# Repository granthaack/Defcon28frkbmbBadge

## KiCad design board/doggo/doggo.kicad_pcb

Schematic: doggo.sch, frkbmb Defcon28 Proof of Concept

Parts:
BT1: Battery_Cell
C1, C3, C4, C6: 100nF; C_0603_1608Metric
C2: 1uF; C_0805_2012Metric
C5: 220nF; C_0603_1608Metric
C7: 10uF
C8: 4.7uF
D1, D2, D3, D4, D5, D6, D7, D8, D9, D10, D11, D12, D13, D14, D15, D16, D17, D18, D19, D20, D21, D22, D23, D24, D25, D26, D27, D28, D29, D30, D31, D32, D33, D34, D35, D36, D37, D38, D39, D40, D41, D42, D43, D44, D45, D46, D47, D48, D49, D50, D51, D52, D53, D54, D55, D56, D57, D58, D59, D60, D61, D62, D63, D64, D65, D66, D67, D68, D69, D70, D71, D72, D73, D74, D75, D76, D77, D78, D79, D80, D81, D82, D83, D84, D85, D86, D87, D88, D89, D90, D91, D92, D93, D94, D95, D96, D97, D98, D99, D100, D101, D102, D103, D104, D105, D106, D107, D108, D109, D110, D111, D112, D113, D114, D115, D116, D117, D118, D119, D120, D121, D122, D123, D124, D125, D126, D127, D128, D129, D130, D131, D132, D133, D134, D135, D136, D137, D138, D139, D140, D141, D142, D143, D144: LED; D_0402_1005Metric
F1: Polyfuse
JP1: Jumper_2_Open
L1: 4.7uH
R1, R2, R3: 4.7k; R_0603_1608Metric
R4, R5: 100k; R_0603_1608Metric
R6, R32, R33: 1k; R_0603_1608Metric
R7: 536K; R_0603_1608Metric
R8: 309K; R_0603_1608Metric
SW1: SW_SPST
U1: IS31FL3731
U2: LIS2HH12
U3: STM32F042K6; LQFP-32_7x7mm_P0.8mm
U4: MCP1640; SOT-23-6

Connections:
/AUD: C5.2
/CA1: D1.1 (K), D2.1 (K), D3.1 (K), D4.1 (K), D5.1 (K), D6.1 (K), D7.1 (K), D8.1 (K), D17.2 (A), D33.2 (A), D49.2 (A), D65.2 (A), D81.2 (A), D97.2 (A), D113.2 (A), D129.2 (A), U1.21
/CA2: D1.2 (A), D17.1 (K), D18.1 (K), D19.1 (K), D20.1 (K), D21.1 (K), D22.1 (K), D23.1 (K), D24.1 (K), D34.2 (A), D50.2 (A), D66.2 (A), D82.2 (A), D98.2 (A), D114.2 (A), D130.2 (A), U1.22
/CA3: D2.2 (A), D18.2 (A), D33.1 (K), D34.1 (K), D35.1 (K), D36.1 (K), D37.1 (K), D38.1 (K), D39.1 (K), D40.1 (K), D51.2 (A), D67.2 (A), D83.2 (A), D99.2 (A), D115.2 (A), D131.2 (A), U1.23
/CA4: D3.2 (A), D19.2 (A), D35.2 (A), D49.1 (K), D50.1 (K), D51.1 (K), D52.1 (K), D53.1 (K), D54.1 (K), D55.1 (K), D56.1 (K), D68.2 (A), D84.2 (A), D100.2 (A), D116.2 (A), D132.2 (A), U1.24
/CA5: D4.2 (A), D20.2 (A), D36.2 (A), D52.2 (A), D65.1 (K), D66.1 (K), D67.1 (K), D68.1 (K), D69.1 (K), D70.1 (K), D71.1 (K), D72.1 (K), D85.2 (A), D101.2 (A), D117.2 (A), D133.2 (A), U1.25
/CA6: D5.2 (A), D21.2 (A), D37.2 (A), D53.2 (A), D69.2 (A), D81.1 (K), D82.1 (K), D83.1 (K), D84.1 (K), D85.1 (K), D86.1 (K), D87.1 (K), D88.1 (K), D102.2 (A), D118.2 (A), D134.2 (A), U1.26
/CA7: D6.2 (A), D22.2 (A), D38.2 (A), D54.2 (A), D70.2 (A), D86.2 (A), D97.1 (K), D98.1 (K), D99.1 (K), D100.1 (K), D101.1 (K), D102.1 (K), D103.1 (K), D104.1 (K), D119.2 (A), D135.2 (A), U1.27
/CA8: D7.2 (A), D23.2 (A), D39.2 (A), D55.2 (A), D71.2 (A), D87.2 (A), D103.2 (A), D113.1 (K), D114.1 (K), D115.1 (K), D116.1 (K), D117.1 (K), D118.1 (K), D119.1 (K), D120.1 (K), D136.2 (A), U1.28
/CA9: D8.2 (A), D24.2 (A), D40.2 (A), D56.2 (A), D72.2 (A), D88.2 (A), D104.2 (A), D120.2 (A), D129.1 (K), D130.1 (K), D131.1 (K), D132.1 (K), D133.1 (K), D134.1 (K), D135.1 (K), D136.1 (K), U1.1
/CB1: D9.1 (K), D10.1 (K), D11.1 (K), D12.1 (K), D13.1 (K), D14.1 (K), D15.1 (K), D16.1 (K), D25.2 (A), D41.2 (A), D57.2 (A), D73.2 (A), D89.2 (A), D105.2 (A), D121.2 (A), D137.2 (A), U1.7
/CB2: D9.2 (A), D25.1 (K), D26.1 (K), D27.1 (K), D28.1 (K), D29.1 (K), D30.1 (K), D31.1 (K), D32.1 (K), D42.2 (A), D58.2 (A), D74.2 (A), D90.2 (A), D106.2 (A), D122.2 (A), D138.2 (A), U1.8
/CB3: D10.2 (A), D26.2 (A), D41.1 (K), D42.1 (K), D43.1 (K), D44.1 (K), D45.1 (K), D46.1 (K), D47.1 (K), D48.1 (K), D59.2 (A), D75.2 (A), D91.2 (A), D107.2 (A), D123.2 (A), D139.2 (A), U1.9
/CB4: D11.2 (A), D27.2 (A), D43.2 (A), D57.1 (K), D58.1 (K), D59.1 (K), D60.1 (K), D61.1 (K), D62.1 (K), D63.1 (K), D64.1 (K), D76.2 (A), D92.2 (A), D108.2 (A), D124.2 (A), D140.2 (A), U1.10
/CB5: D12.2 (A), D28.2 (A), D44.2 (A), D60.2 (A), D73.1 (K), D74.1 (K), D75.1 (K), D76.1 (K), D77.1 (K), D78.1 (K), D79.1 (K), D80.1 (K), D93.2 (A), D109.2 (A), D125.2 (A), D141.2 (A), U1.11
/CB6: D13.2 (A), D29.2 (A), D45.2 (A), D61.2 (A), D77.2 (A), D89.1 (K), D90.1 (K), D91.1 (K), D92.1 (K), D93.1 (K), D94.1 (K), D95.1 (K), D96.1 (K), D110.2 (A), D126.2 (A), D142.2 (A), U1.12
/CB7: D14.2 (A), D30.2 (A), D46.2 (A), D62.2 (A), D78.2 (A), D94.2 (A), D105.1 (K), D106.1 (K), D107.1 (K), D108.1 (K), D109.1 (K), D110.1 (K), D111.1 (K), D112.1 (K), D127.2 (A), D143.2 (A), U1.13
/CB8: D15.2 (A), D31.2 (A), D47.2 (A), D63.2 (A), D79.2 (A), D95.2 (A), D111.2 (A), D121.1 (K), D122.1 (K), D123.1 (K), D124.1 (K), D125.1 (K), D126.1 (K), D127.1 (K), D128.1 (K), D144.2 (A), U1.14
/CB9: D16.2 (A), D32.2 (A), D48.2 (A), D64.2 (A), D80.2 (A), D96.2 (A), D112.2 (A), D128.2 (A), D137.1 (K), D138.1 (K), D139.1 (K), D140.1 (K), D141.1 (K), D142.1 (K), D143.1 (K), D144.1 (K), U1.15
/CS: R33.2, U2.2
/INT1: U2.12
/INT2: U2.11
/INTB: R1.1, U1.4
/SA0_SDO: R32.2, U2.3
/SCL: R2.1, U1.20, U2.1, U3.29 (PB6)
/SDA: R3.1, U1.19, U2.4, U3.20 (PA10)
GND: C1.1, C2.1, C3.1, C4.2, C6.2, R4.1, R5.1, R8.2, U1.5, U1.18, U1.29, U2.5, U2.6, U2.7, U2.8, U3.16 (VSS), U3.32 (VSS), U4.2
unnamed: C1.2, U1.16
unnamed: C5.1, U1.17
unnamed: U4.3, U4.6
unnamed: R6.2, U3.4 (NRST)
unnamed: R5.2, U1.6
unnamed: R7.2, R8.1, U4.4

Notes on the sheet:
Accelerometer

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
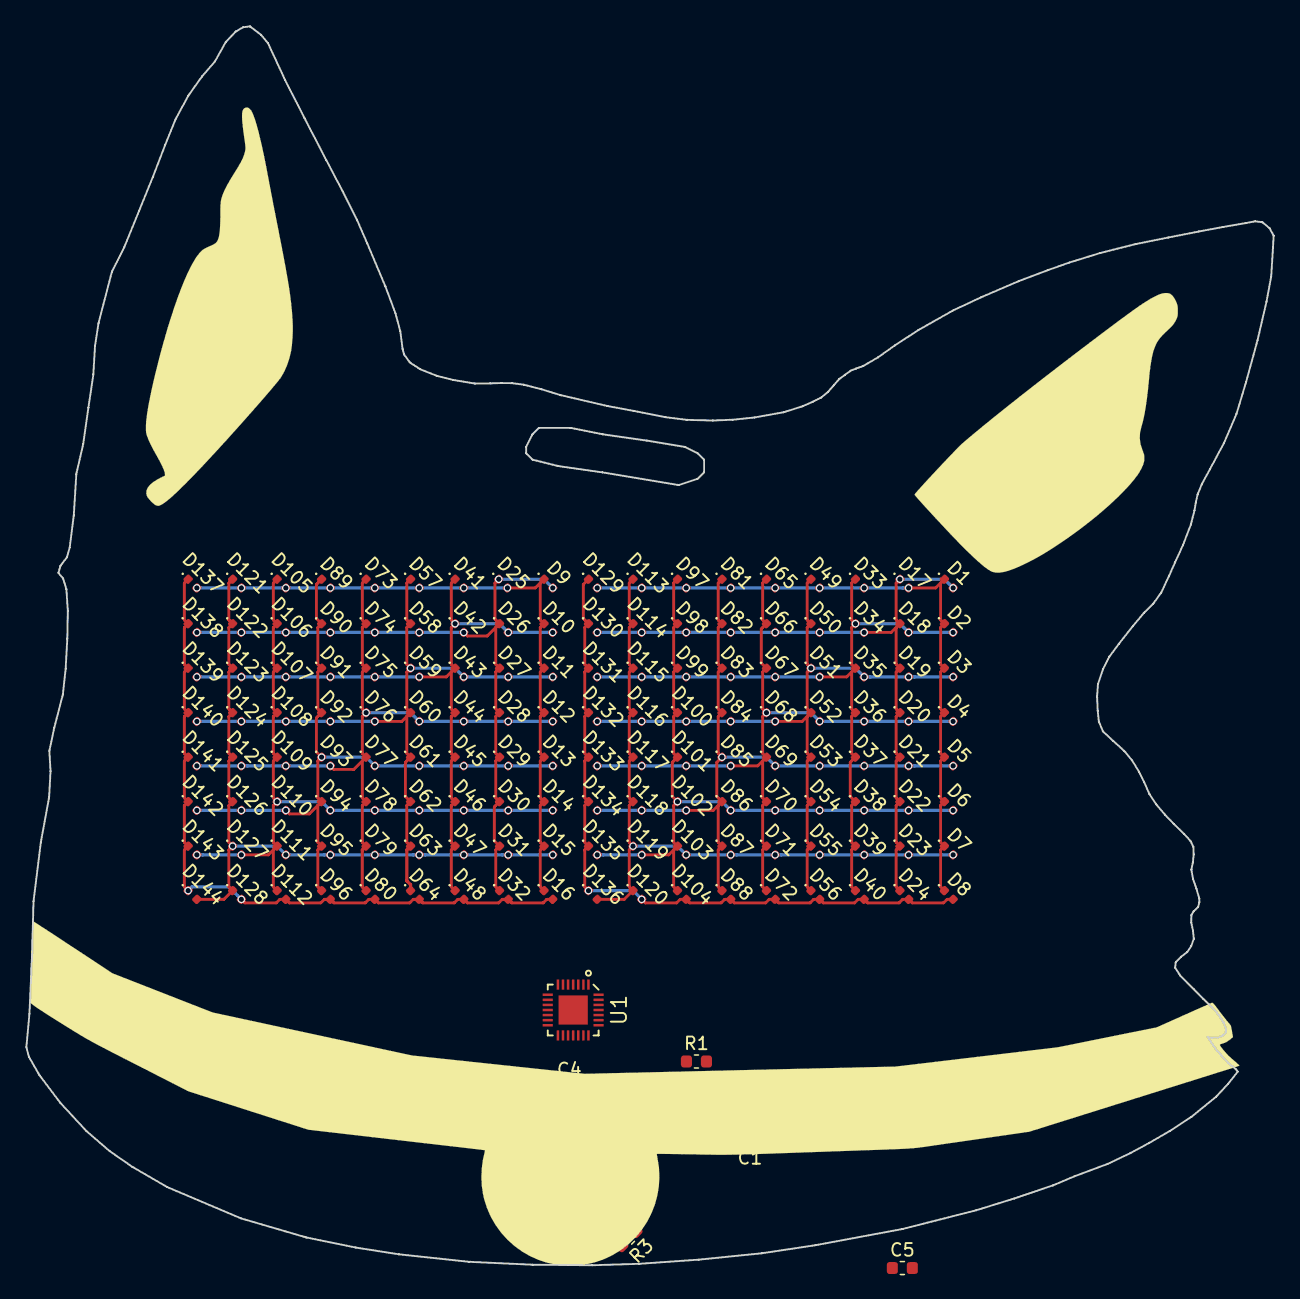
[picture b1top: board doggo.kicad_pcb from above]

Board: 2 copper layers, 98.1 x 97.5 mm, 164 parts (0 on the bottom side), 32 nets.

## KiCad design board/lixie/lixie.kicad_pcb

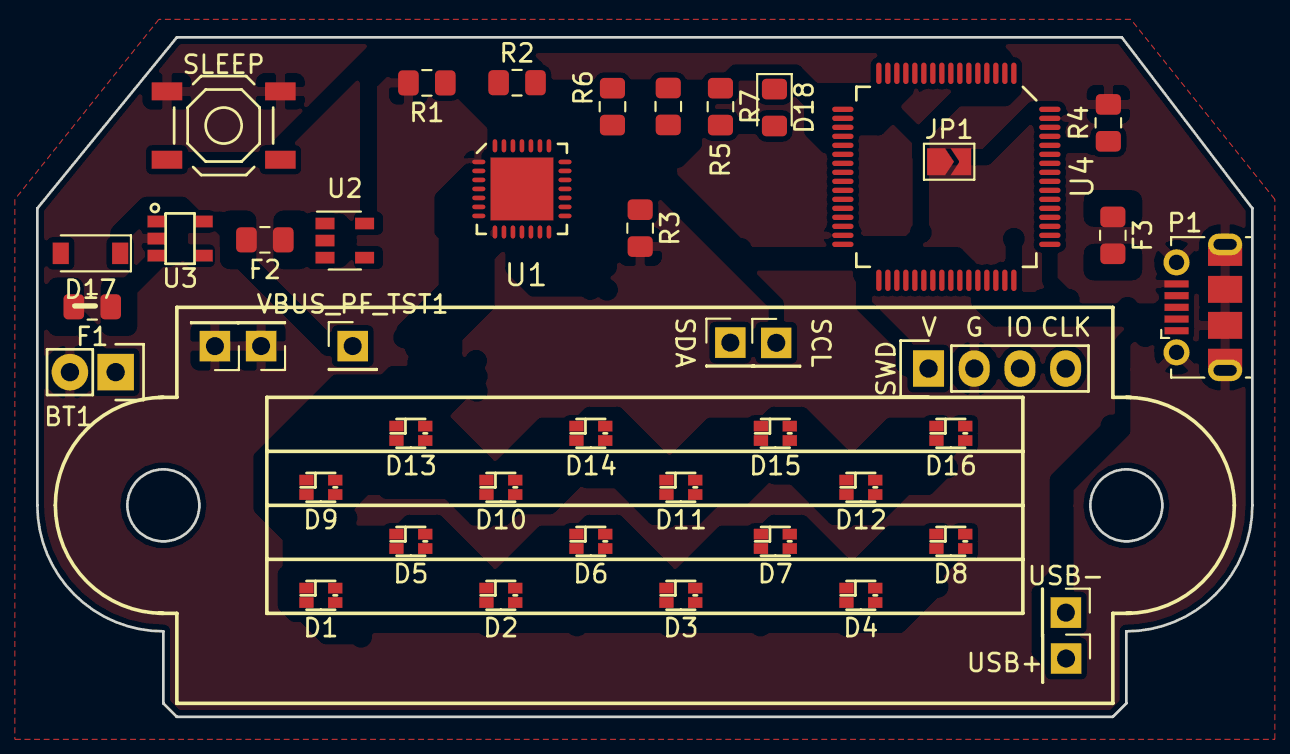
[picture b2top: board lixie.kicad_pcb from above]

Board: 2 copper layers, 67.5 x 37.8 mm, 44 parts (0 on the bottom side), 36 nets, no tracks yet.

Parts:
BT1: Battery_Cell; Pin_Header_Straight_1x02
D1, D2, D3, D4, D5, D6, D7, D8, D9, D10, D11, D12, D13, D14, D15, D16: LED_ARBG; LED_LSTD_0606
D17: D; D_SOD-123
D18: LED; LED_0805_2012Metric_Pad1.15x1.40mm_HandSolder
F1, F2, F3: Polyfuse; Fuse_0805_2012Metric_Pad1.15x1.40mm_HandSolder
JP1: Jumper_2_Open; SolderJumper-2_P1.3mm_Open_TrianglePad1.0x1.5mm
P1: USB_OTG; USB_Micro-B_Molex-105017-0001
R1, R2: 4.7k; R_0805_2012Metric_Pad1.15x1.40mm_HandSolder
R3, R4, R5: 100k; R_0805_2012Metric_Pad1.15x1.40mm_HandSolder
R6: R; R_0805_2012Metric_Pad1.15x1.40mm_HandSolder
R7: 10k; R_0805_2012Metric_Pad1.15x1.40mm_HandSolder
SCL_TST1: TestPoint; PinHeader_1x01_P2.54mm_Vertical
SDA_TST1: TestPoint; PinHeader_1x01_P2.54mm_Vertical
SLEEP: SW_Push; SW_SPST_TL3342
SWD: CONN_01X04; Pin_Header_Straight_1x04
U1: IS31FL3738
U2: MAX40200
U3: MIC550x
U4: STM32L073xZ; STM32L073RZT3
USB_DM_TST1: TestPoint; PinHeader_1x01_P2.54mm_Vertical
USB_DP_GND1, USB_DP_GND2: TestPoint; PinHeader_1x01_P2.54mm_Vertical
USB_DP_TST1: TestPoint; PinHeader_1x01_P2.54mm_Vertical
VBUS_PF_TST1: TestPoint; PinHeader_1x01_P2.54mm_Vertical

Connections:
+3V3: R1.1, R2.1, R4.2, R6.1, SWD.1, U1.22, U3.5, U4.1, U4.13, U4.19, U4.32, U4.64
+5V: F3.1, P1.1
+BATT: BT1.1, F1.2
/BOOT0: R7.1, U4.60
/CRASH_LED: D18.1, U4.21
/INTB: R4.1, U1.27
/LED_CURRENT: R5.1, U1.20
/NRST: JP1.2, U4.7
/SCL: R2.2, SCL_TST1.1, U1.25, U4.42
/SDA: R1.2, SDA_TST1.1, U1.24, U4.43
/SDB: R3.1, U1.28
/SWCLK: SWD.4, U4.49
/SWDIO: SWD.3, U4.46
/USB_DM: P1.2, U4.44, USB_DM_TST1.1
/USB_DP: P1.3, U4.45, USB_DP_TST1.1
GND: BT1.2, JP1.1, P1.5, P1.6, R3.2, R5.2, R7.2, SLEEP.1, SWD.2, U1.1, U1.4, U1.8, U1.26, U1.29, U2.2, U3.2, U4.12, U4.18, U4.31, U4.47, U4.63, USB_DP_GND1.1, USB_DP_GND2.1
unnamed: D1.1, D9.1, U1.10
unnamed: D1.2, D2.2, D3.2, D4.2, D5.2, D6.2, D7.2, D8.2, U1.9
unnamed: D1.3, D2.3, D3.3, D4.3, D5.3, D6.3, D7.3, D8.3, U1.6
unnamed: D1.4, D2.4, D3.4, D4.4, D5.4, D6.4, D7.4, D8.4, U1.7
unnamed: D2.1, D10.1, U1.11
unnamed: D9.2, D10.2, D11.2, D12.2, D13.2, D14.2, D15.2, D16.2, U1.5
unnamed: D9.3, D10.3, D11.3, D12.3, D13.3, D14.3, D15.3, D16.3, U1.2
unnamed: D9.4, D10.4, D11.4, D12.4, D13.4, D14.4, D15.4, D16.4, U1.3
unnamed: D3.1, D11.1, U1.13
unnamed: D4.1, D12.1, U1.14
unnamed: D5.1, D13.1, U1.15
unnamed: D6.1, D14.1, U1.16
unnamed: D7.1, D15.1, U1.18
unnamed: D8.1, D16.1, U1.19
unnamed: D17.1, F2.2, U2.5, VBUS_PF_TST1.1
unnamed: D17.2, F3.2
unnamed: D18.2, R6.2
unnamed: F1.1, U2.1, U2.3
unnamed: SLEEP.2, U4.2
VBUS: F2.1, U1.12, U1.17, U1.21, U3.1, U3.3, U4.48

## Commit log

2019-08-12 created schematic for prototype
2019-08-12 work on prototype LED matrix
2019-08-13 more routing on prototype
2019-08-14 moved stuff around and made schematic lib for different LED matrix driver
2019-08-15 made matrix for new LED driver. TODO: Redo the accelerometer footprint because it's slightly off due to how the wizard works
2019-08-15 ready to start laying out new board
2019-08-22 organized the LEDs on the prototype
2019-08-25 ready to export gerbers, waiting on approval from group
2019-09-04 more work on the SAOs
2019-09-05 work on punching popuko sao
2020-01-16 wired power and LED matrix
2020-01-20 got basic tokenizer working
2020-01-20 added game syntax and changed some of the token values
2020-01-21 testing to see if cubeIDE will delete all my private files
2020-01-21 Created structs and prototypes for rooms, objects, and items.
2020-01-21 updated syntax checker
2020-01-22 declared all the room, item, and object objects
2020-01-22 wrote some prototypes for tomorrows work
2020-01-22 added tokens for rooms
2020-01-23 Got invalid input prints working
2020-01-26 got movement and location working
2020-02-02 got use and get tokens working
2020-02-02 made some footprints, fixed the power diode circuitry
2020-02-03 started working on layout
2020-02-09 got low power mode working
2020-02-09 wrote a deepsleep function
2020-02-10 laid out the board
2020-02-15 saving old stuff just in case
2020-02-16 added some test points
2020-02-16 got item mixing working
2020-02-17 apparently I routed EVERY FUCKING LED WRONG so now I gotta fix it
2020-02-17 kicad crashed so now I am wiring the LEDs for a fucking 3rd time
2020-02-18 made artwork, rewired the LEDs
2020-03-08 got the first puzzle done
2020-05-10 working on a cancelled badge
2020-05-11 got a rotating square but I cheated
2020-05-12 started work on dog boarD
2020-05-12 laying out LEDs
2020-05-15 finally got the FUCKING svg2shenzen to barely work enough so I could hack together a footprint
2020-05-18 worked on power support, layed out LED array
2020-05-18 got accelerometer working:
2020-05-18 added todos
2020-05-24 got accelerometer working properly, realized calculating angles is dumb
2020-05-25 added eyes that look around
2020-05-26 got all the footprints on the board
